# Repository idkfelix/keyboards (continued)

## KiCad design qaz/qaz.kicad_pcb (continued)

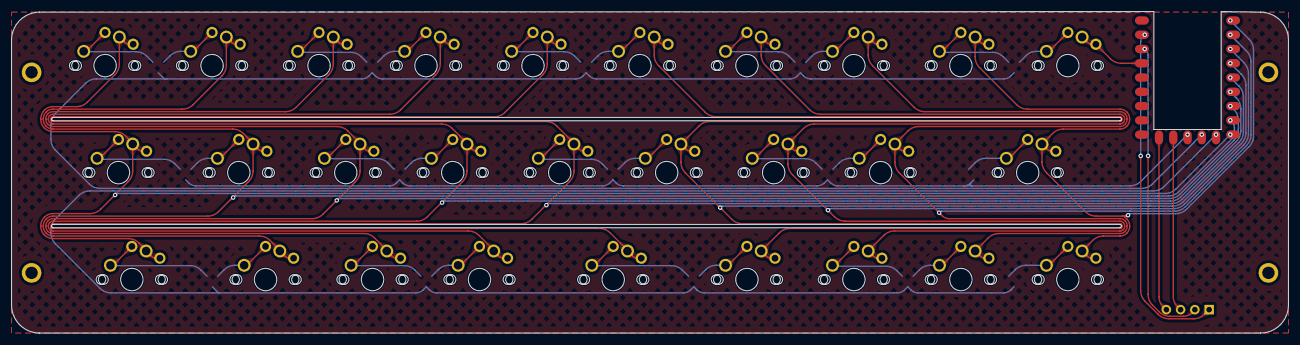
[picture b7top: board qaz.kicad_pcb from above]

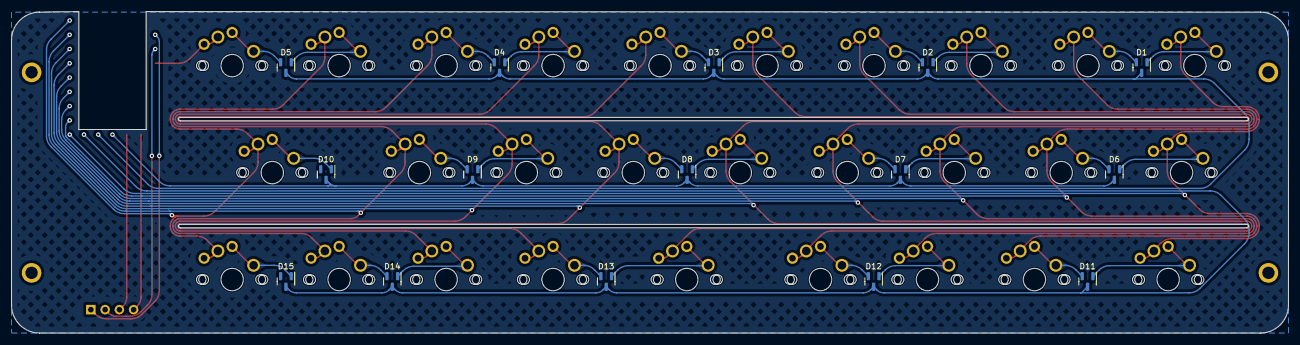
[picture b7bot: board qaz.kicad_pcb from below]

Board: 2 copper layers, 227.4 x 57.2 mm, 45 parts (15 on the bottom side), 45 nets.

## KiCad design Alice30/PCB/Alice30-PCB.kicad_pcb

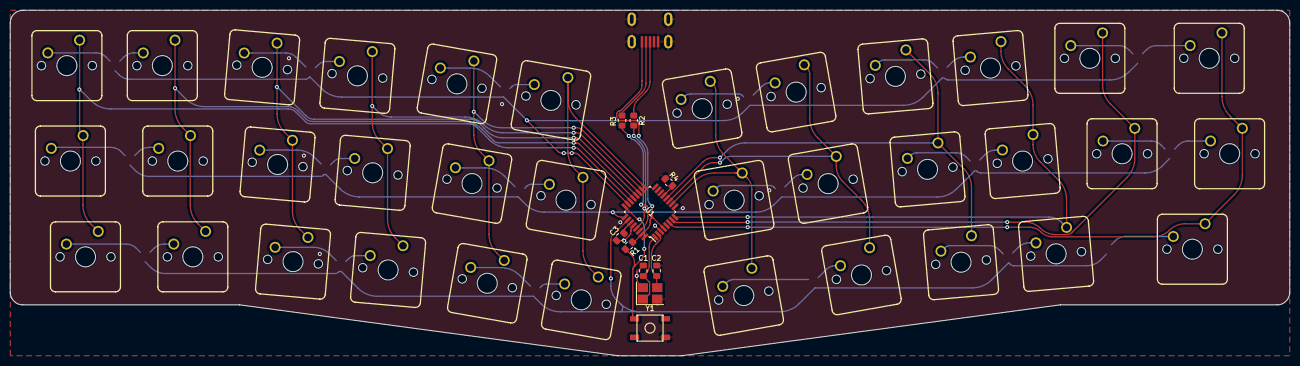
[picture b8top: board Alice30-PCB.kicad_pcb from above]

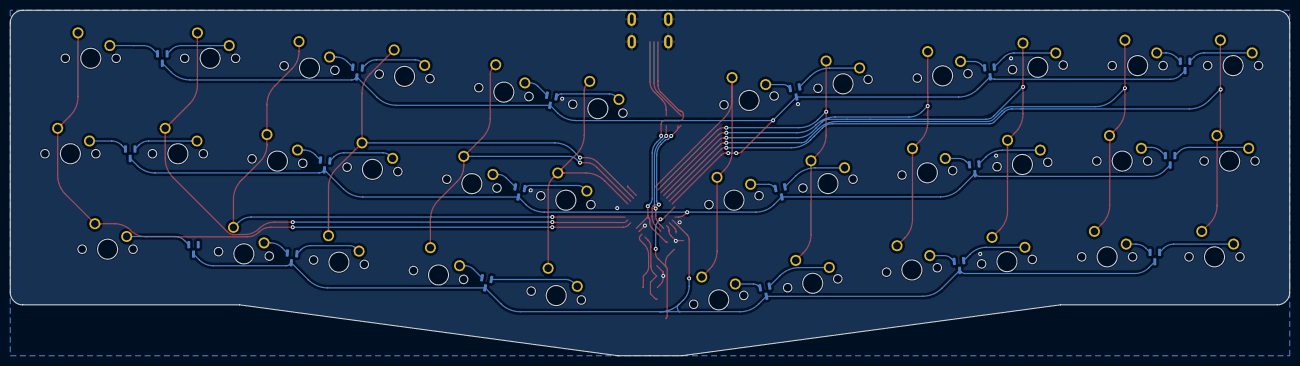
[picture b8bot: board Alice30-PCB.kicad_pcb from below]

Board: 2 copper layers, 255.4 x 69.0 mm, 64 parts (18 on the bottom side), 61 nets.

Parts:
C1, C2: 22pf; C_0805_2012Metric_Pad1.18x1.45mm_HandSolder
C3: 1uf; C_0805_2012Metric_Pad1.18x1.45mm_HandSolder
D1, D2, D3, D4, D5, D6, D7, D8, D9, D10, D11, D12, D13, D14, D15, D16, D17, D18: BAV70; SOT-23
J1: USB_B_Mini; Molex-0548190589
R1, R2, R3, R4: 10k; R_0805_2012Metric_Pad1.20x1.40mm_HandSolder
SW1, SW2, SW3, SW4, SW5, SW6, SW7, SW8, SW9, SW10, SW11, SW14, SW15, SW16, SW17, SW18, SW19, SW20, SW21, SW22, SW23, SW26, SW27, SW28, SW29, SW30, SW32, SW33, SW34: SW_Push_45deg; MX_1U
SW12, SW31: SW_Push_45deg; MX_1.5U
SW13, SW24, SW25: SW_Push_45deg; MX_1.25U
SW35: SW_Push_45deg; MX_1.75U
SW36: SW_Push; SKQG-1155865
U1: ATmega32U2-A; TQFP-32_7x7mm_P0.8mm
Y1: Crystal_GND24_Small; Crystal_SMD_3225-4Pin_3.2x2.5mm_HandSoldering

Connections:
+5V: J1.1 (VBUS), R1.1, U1.4 (VCC), U1.31 (UVCC)
GND: C1.1, C2.1, C3.1, J1.5 (GND), J1.6 (Shield), R4.2, SW36.1, U1.3 (GND), U1.28 (UGND), Y1.2, Y1.4
unnamed: D1.1 (A), SW1.2
unnamed: D1.2 (A), SW2.2
unnamed: D2.1 (A), SW3.2
unnamed: D2.2 (A), SW4.2
unnamed: D3.1 (A), SW5.2
unnamed: D3.2 (A), SW6.2
unnamed: D4.1 (A), SW7.2
unnamed: D4.2 (A), SW8.2
unnamed: D5.1 (A), SW9.2
unnamed: D5.2 (A), SW10.2
unnamed: D6.1 (A), SW11.2
unnamed: D6.2 (A), SW12.2
unnamed: D7.1 (A), SW13.2
unnamed: D7.2 (A), SW14.2
unnamed: D8.1 (A), SW15.2
unnamed: D8.2 (A), SW16.2
unnamed: D9.1 (A), SW17.2
unnamed: D9.2 (A), SW18.2
unnamed: D10.1 (A), SW19.2
unnamed: D10.2 (A), SW20.2
unnamed: D11.1 (A), SW21.2
unnamed: D11.2 (A), SW22.2
unnamed: D12.1 (A), SW23.2
unnamed: D12.2 (A), SW24.2
unnamed: D13.1 (A), SW25.2
unnamed: D13.2 (A), SW26.2
unnamed: D14.1 (A), SW27.2
unnamed: D14.2 (A), SW28.2
unnamed: D15.1 (A), SW29.2
unnamed: D15.2 (A), SW30.2
unnamed: D16.1 (A), SW31.2
unnamed: D16.2 (A), SW32.2
unnamed: D17.1 (A), SW33.2
unnamed: D17.2 (A), SW34.2
unnamed: D18.2 (A), SW35.2
unnamed: J1.3 (D+), R2.1
unnamed: J1.2 (D-), R3.1
unnamed: R2.2, U1.29 (D+)
unnamed: R3.2, U1.30 (D-)
unnamed: C2.2, U1.2 (PC0/XTAL2), Y1.3
unnamed: R1.2, SW36.2, U1.24 (PC1/~RESET)
unnamed: C3.2, U1.27 (UCAP)
unnamed: C1.2, U1.1 (XTAL1), Y1.1
unnamed: R4.1, U1.13 (~HWB/PD7)
c1: SW1.1, SW13.1, SW25.1
c2: SW2.1, SW14.1, SW26.1, U1.21 (PB7)
c3: SW3.1, SW15.1, SW27.1, U1.20 (PB6)
c4: SW4.1, SW16.1, SW28.1, U1.19 (PB5)
c5: SW5.1, SW17.1, SW29.1, U1.18 (PB4)
c6: SW6.1, SW18.1, SW30.1, U1.17 (PB3)
c7: SW7.1, SW19.1, SW31.1, U1.10 (PD4)
c8: SW8.1, SW20.1, SW32.1, U1.11 (PD5)
c9: SW9.1, SW21.1, SW33.1, U1.12 (PD6)
c10: SW10.1, SW22.1, SW34.1, U1.8 (PD2)
c11: SW11.1, SW23.1, U1.7 (PD1)
c12: SW12.1, SW24.1, SW35.1, U1.6 (PD0)
r1: D1.3 (K), D2.3 (K), D3.3 (K), D4.3 (K), D5.3 (K), D6.3 (K), U1.23 (PC6)
r2: D7.3 (K), D8.3 (K), D9.3 (K), D10.3 (K), D11.3 (K), D12.3 (K), U1.25 (PC5)
r3: D13.3 (K), D14.3 (K), D15.3 (K), D16.3 (K), D17.3 (K), D18.3 (K), U1.26 (PC4)
